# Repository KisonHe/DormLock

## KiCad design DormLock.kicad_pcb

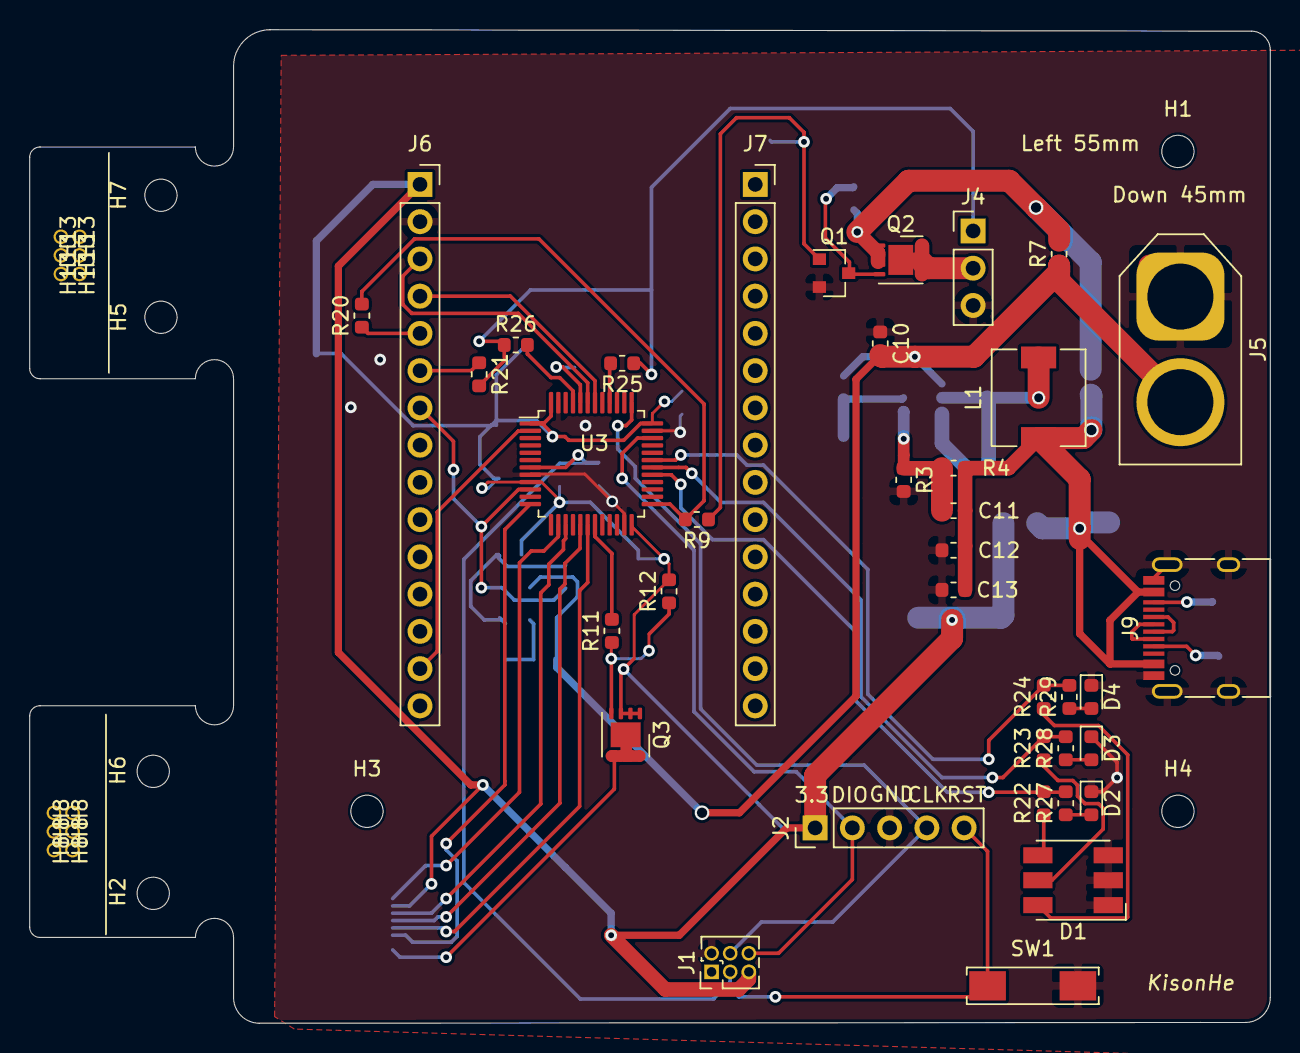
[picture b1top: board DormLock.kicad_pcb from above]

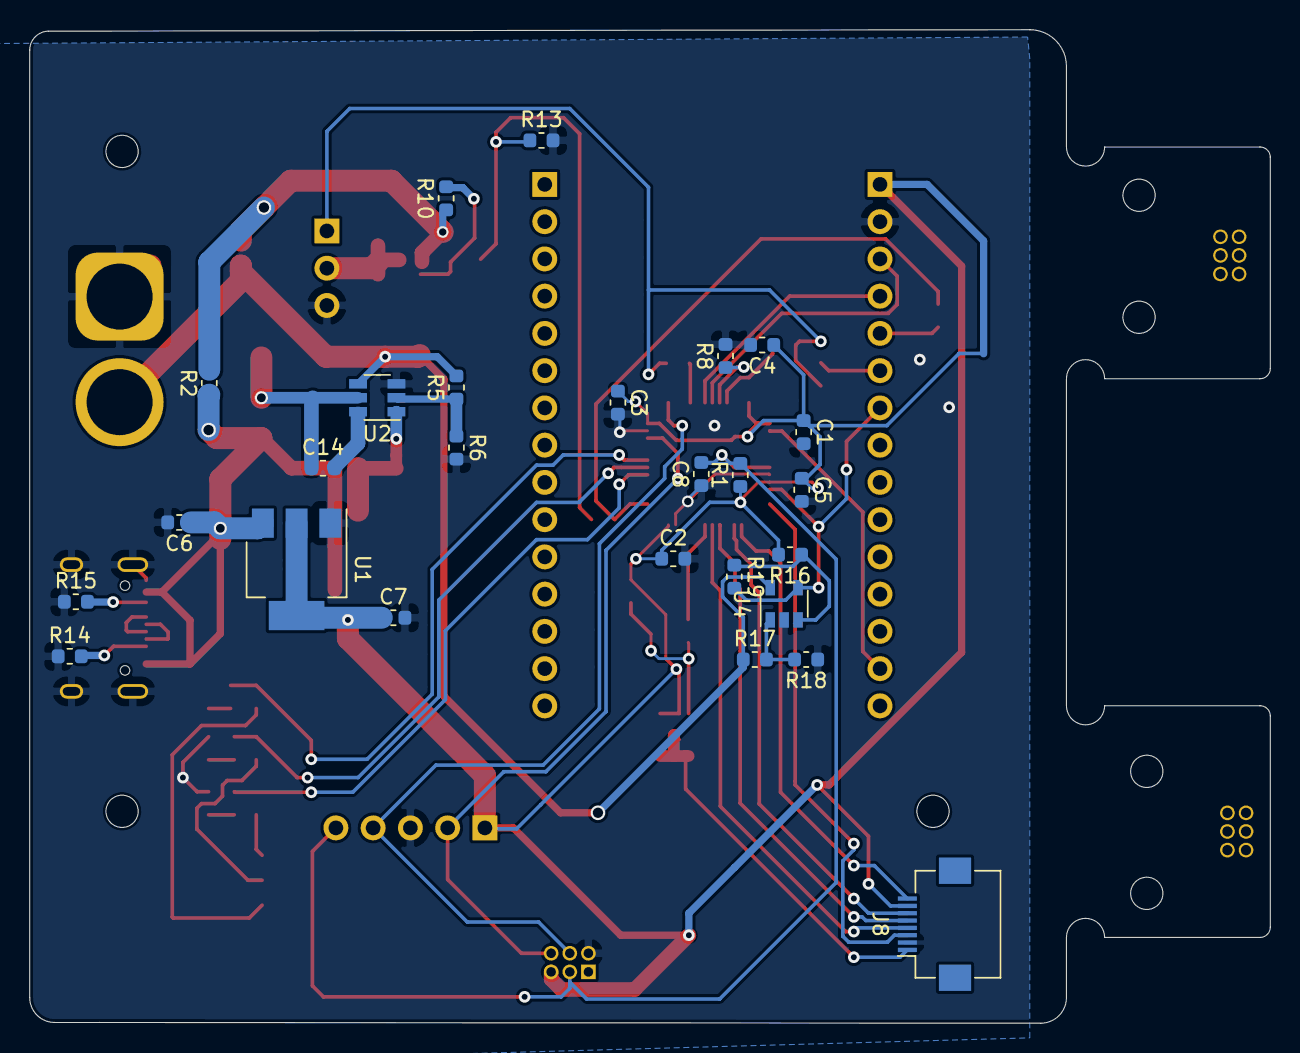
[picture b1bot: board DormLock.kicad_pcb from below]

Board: 2 copper layers, 84.6 x 67.8 mm, 82 parts (26 on the bottom side), 49 nets.

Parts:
C1, C2, C3, C4, C5, C8, C14: 100nf; C_0603_1608Metric
C6: 1uf; C_0603_1608Metric
C7: 2.2uf; C_0603_1608Metric
C10: 10uf; C_0603_1608Metric
C11: 47pf; C_0603_1608Metric
C12, C13: 22uf; C_0603_1608Metric
D1: LED_RGB; LED_RGB_5050-6
D2, D3, D4: LED; LED_0603_1608Metric
H1, H2, H3, H4, H5, H6, H7: MountingHole; MountingHole_2.2mm_M2_DIN965
H8, H8#2, H8#3, H8#4, H8#5, H8#6, H13, H13#2, H13#3, H13#4, H13#5, H13#6: 0.7mm Hole; 0.7mmInR Hole
J1: Conn_02x03_Odd_Even; PinHeader_2x03_P1.27mm_Vertical
J2: Conn_01x05; PinHeader_1x05_P2.54mm_Vertical
J4: Conn_01x03; PinHeader_1x03_P2.54mm_Vertical
J5: Conn_01x02; AMASS_XT60-M_1x02_P7.20mm_Vertical
J6, J7: Conn_01x15; PinSocket_1x15_P2.54mm_Vertical
J8: Conn_01x08; Hirose_FH12-8S-0.5SH_1x08-1MP_P0.50mm_Horizontal
J9: USB_C_Receptacle; USB_C_Receptacle_HRO_TYPE-C-31-M-12
L1: 4.7uh; L_6.3x6.3_H3
Q1: Q_NPN_BEC; SOT-23
Q2, Q3: Q_PMOS_GSD; DFN-8-1EP_3x3mm_P0.65mm_EP1.7x2.05mm
R1: 10K; R_0603_1608Metric
R2, R5, R7, R20, R21, R25, R26: 0; R_0603_1608Metric
R3: 13.7k; R_0603_1608Metric
R4, R8, R13: 100k; R_0603_1608Metric
R6, R12, R16, R17, R19: 10k; R_0603_1608Metric
R9, R10, R22, R23, R24, R27, R28, R29: 2.2k; R_0603_1608Metric
R11: 1k; R_0603_1608Metric
R14, R15, R18: 5.1k; R_0603_1608Metric
SW1: SW_Push; SW_SPST_REED_CT05-XXXX-J1
U1: SPX1117M3-L-3-3/TR; SOT-223-3_TabPin2
U2: SY8105; TSOT-23-6
U3: STM32F030CCTx; LQFP-48_7x7mm_P0.5mm
U4: LM321; SOT-23-5

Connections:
+3V3: C1.1, C2.1, C3.1, C4.1, C5.1, C7.1, J1.5, J2.1, J6.1, J8.7, Q3.2, R1.1, R12.2, R16.2, U1.2, U3.1, U3.9, U3.24, U3.36, U3.48
+5V: C6.1, C11.2, C12.2, C13.2, J9.A4, J9.A9, J9.B4, J9.B9, L1.1, R2.1, R4.2, U1.3
+BATT: C10.2, J5.2, R5.2, R7.1, R17.1, U2.4, U4.5
/BATT_AD: J6.7, R19.2, U3.10, U4.4
/CS: J8.8, U3.14
/DC: J8.4, U3.18
/LEDA: J8.1, Q3.3
/LEDA_32: R11.2, U3.19
/RESET: J8.3, U3.12
/RGB_B: R22.2, R27.2, U3.29
/RGB_G: R23.2, R28.2, U3.30
/RGB_R: R24.2, R29.2, U3.31
/SCL: J8.6, U3.15
/SDA: J8.5, U3.17
/STEER_EN: R9.2, R20.2, U3.25
/STEER_EN_8266: J6.5, R20.1
/STEER_PWM: J4.1, R21.2, R25.1, R26.1
/STEER_PWM_8266: J6.6, R21.1
/STMSYS_WAKEUP2: J6.14, U3.2
/STM_NRST: C8.2, J1.3, J2.5, R1.2, SW1.2, U3.7
/STM_SWCLK: J1.4, J2.4, U3.37
/STM_SWDIO: J1.6, J2.2, U3.34
/UART_32RX: J6.3, U3.43
/UART_32TX: J6.4, U3.42
/VOutput: J4.2, Q2.3
GND: C1.2, C2.2, C3.2, C4.2, C5.2, C6.2, C7.2, C8.1, C10.1, C12.1, C13.1, D1.1, D1.2, D1.3, D2.1, D3.1, D4.1, J1.2, J2.3, J4.3, J5.1, J6.2, J8.2, J9.A1, J9.A12, J9.B1, J9.B12, J9.S1, Q1.2, R3.2, R6.2, R8.2, R13.2, R14.1, R15.1, R18.1, SW1.1, U1.1, U2.3, U3.8, U3.23, U3.35, U3.47, U4.2
unnamed: C11.1, R3.1, R4.1, U2.1
unnamed: C14.1, L1.2, U2.5
unnamed: C14.2, U2.6
unnamed: D1.4, R22.1
unnamed: D1.5, R23.1
unnamed: D1.6, R24.1
unnamed: D2.2, R27.1
unnamed: D3.2, R28.1
unnamed: D4.2, R29.1
unnamed: J9.A5, R14.2
unnamed: J9.A6, J9.B6
unnamed: J9.A7, J9.B7
unnamed: J9.B5, R15.2
unnamed: Q1.1, R9.1, R13.1
unnamed: Q1.3, Q2.1, R10.2
unnamed: Q3.1, R11.1, R12.1
unnamed: R5.1, R6.1, U2.2
unnamed: R8.1, U3.44
unnamed: R16.1, R19.1, U4.3
unnamed: R17.2, R18.2, U4.1
unnamed: R25.2, U3.40
unnamed: R26.2, U3.45
Vdrive: Q2.2, R2.2, R7.2, R10.1

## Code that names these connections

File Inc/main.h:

/* USER CODE BEGIN Header */
/**
  ******************************************************************************
  * @file           : main.h
  * @brief          : Header for main.c file.
  *                   This file contains the common defines of the application.
  ******************************************************************************
  * @attention
  *
  * <h2><center>&copy; Copyright (c) 2020 STMicroelectronics.
  * All rights reserved.</center></h2>
  *
  * This software component is licensed by ST under Ultimate Liberty license
  * SLA0044, the "License"; You may not use this file except in compliance with
  * the License. You may obtain a copy of the License at:
  *                             www.st.com/SLA0044
  *
  ******************************************************************************
  */
/* USER CODE END Header */

/* Define to prevent recursive inclusion -------------------------------------*/
#ifndef __MAIN_H
#define __MAIN_H

#ifdef __cplusplus
extern "C" {
#endif

/* Includes ------------------------------------------------------------------*/
#include "stm32f0xx_hal.h"

/* Private includes ----------------------------------------------------------*/
/* USER CODE BEGIN Includes */

/* USER CODE END Includes */

/* Exported types ------------------------------------------------------------*/
/* USER CODE BEGIN ET */

/* USER CODE END ET */

/* Exported constants --------------------------------------------------------*/
/* USER CODE BEGIN EC */

/* USER CODE END EC */

/* Exported macro ------------------------------------------------------------*/
/* USER CODE BEGIN EM */

/* USER CODE END EM */

/* Exported functions prototypes ---------------------------------------------*/
void Error_Handler(void);

/* USER CODE BEGIN EFP */

/* USER CODE END EFP */

/* Private defines -----------------------------------------------------------*/
#define IPS_RESET_Pin GPIO_PIN_2
#define IPS_RESET_GPIO_Port GPIOA
#define SCREEN_CS_Pin GPIO_PIN_4
#define SCREEN_CS_GPIO_Port GPIOA
#define IPS_DC_Pin GPIO_PIN_0
#define IPS_DC_GPIO_Port GPIOB
#define SCREEN_BRIGHTNESS_Pin GPIO_PIN_1
#define SCREEN_BRIGHTNESS_GPIO_Port GPIOB
#define STEER_EN_Pin GPIO_PIN_12
#define STEER_EN_GPIO_Port GPIOB
#define RGB_B_Pin GPIO_PIN_8
#define RGB_B_GPIO_Port GPIOA
#define RGB_G_Pin GPIO_PIN_9
#define RGB_G_GPIO_Port GPIOA
#define RGB_R_Pin GPIO_PIN_10
#define RGB_R_GPIO_Port GPIOA
#define STEER_PWM_B_Pin GPIO_PIN_4
#define STEER_PWM_B_GPIO_Port GPIOB
#define STEER_PWM_Pin GPIO_PIN_8
#define STEER_PWM_GPIO_Port GPIOB
/* USER CODE BEGIN Private defines */

/* USER CODE END Private defines */

#ifdef __cplusplus
}
#endif

#endif /* __MAIN_H */

/************************ (C) COPYRIGHT STMicroelectronics *****END OF FILE****/

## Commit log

2020-09-08 V0.1
2020-09-09 V0.2
2020-09-09 V0.25
2020-09-09 V0.29
2020-09-09 V1.0
2020-09-09 Added ClionProject
2020-09-22 V1.1
2020-09-23 V1.2
2020-09-23 Update UART IRQ
2020-09-24 V2.0
2020-09-25 Backup
2020-10-05 Embeded Ver 1.0
2020-10-05 PCBV3.0
2020-10-09 Add nodemcu side battery report
2020-10-11 HalfDone RGB Queue. Apply to new hardware
2020-10-12 Add ADC and UART reply.
2020-10-12 Better cfg
2020-10-12 Change Comments. Calibrated Batty Value
2020-10-27 Auto Wifi Reconnect. ADC run once at init.
2021-03-11 change ignore
2021-06-04 Move to ESP32
    Use eps32 + BLE + web bluetooth instead
